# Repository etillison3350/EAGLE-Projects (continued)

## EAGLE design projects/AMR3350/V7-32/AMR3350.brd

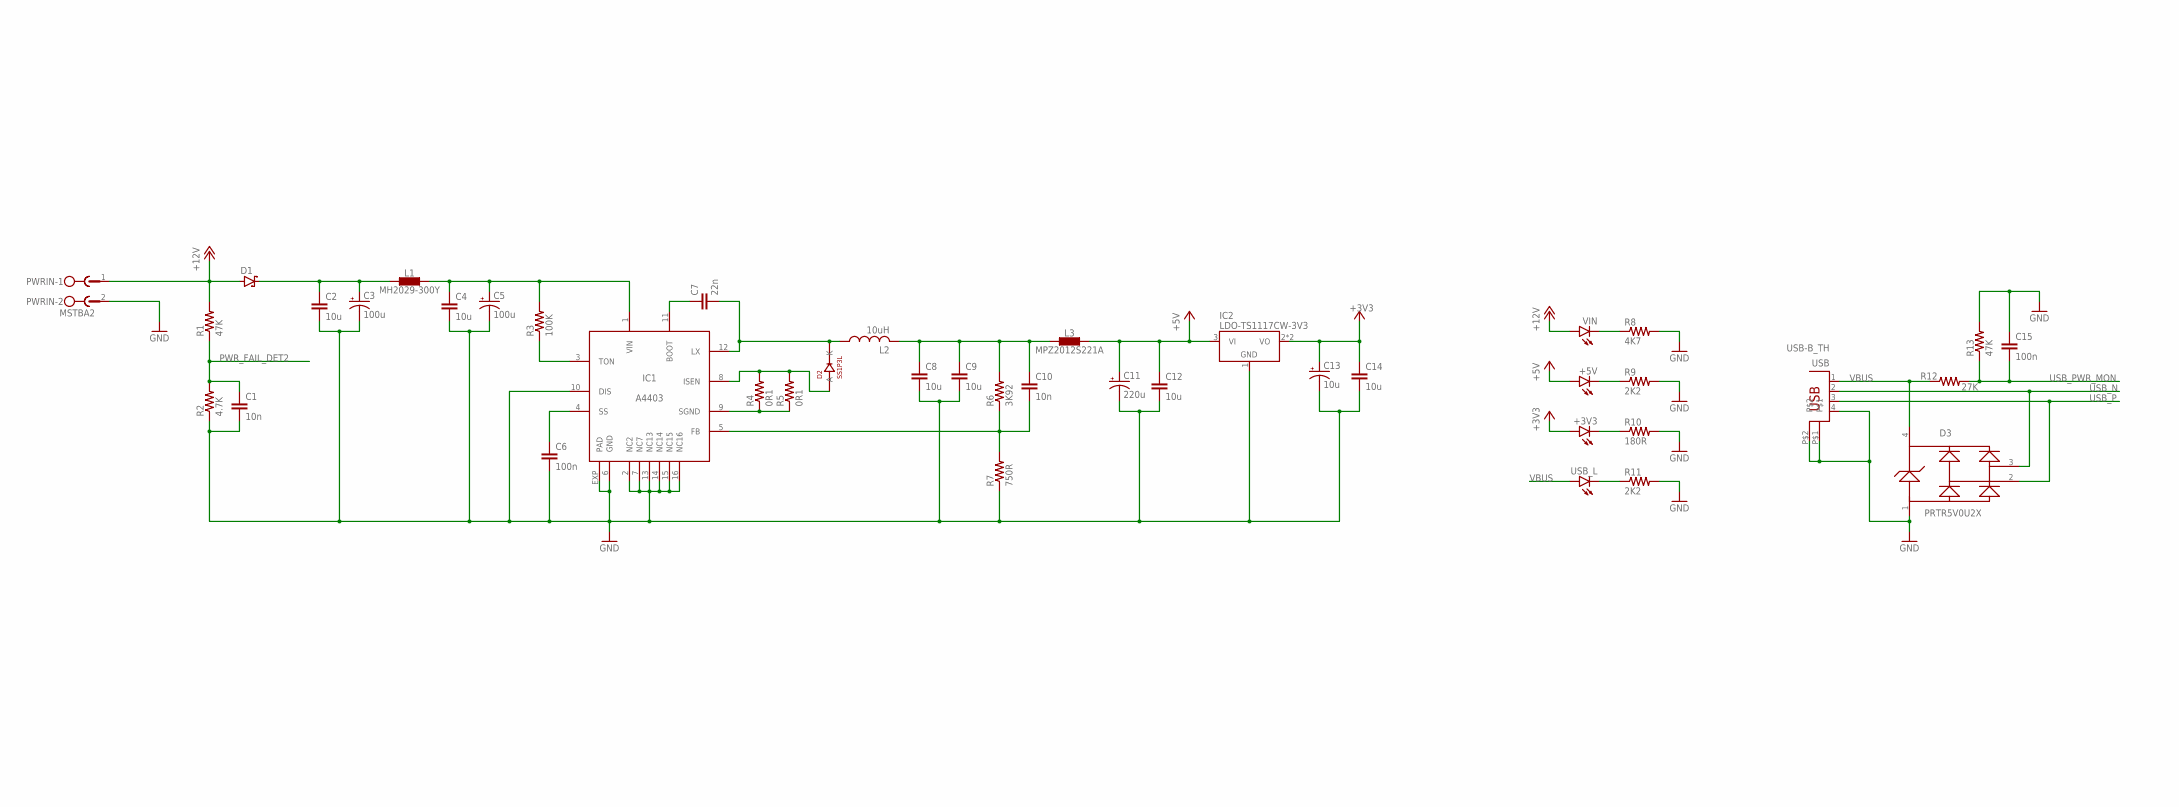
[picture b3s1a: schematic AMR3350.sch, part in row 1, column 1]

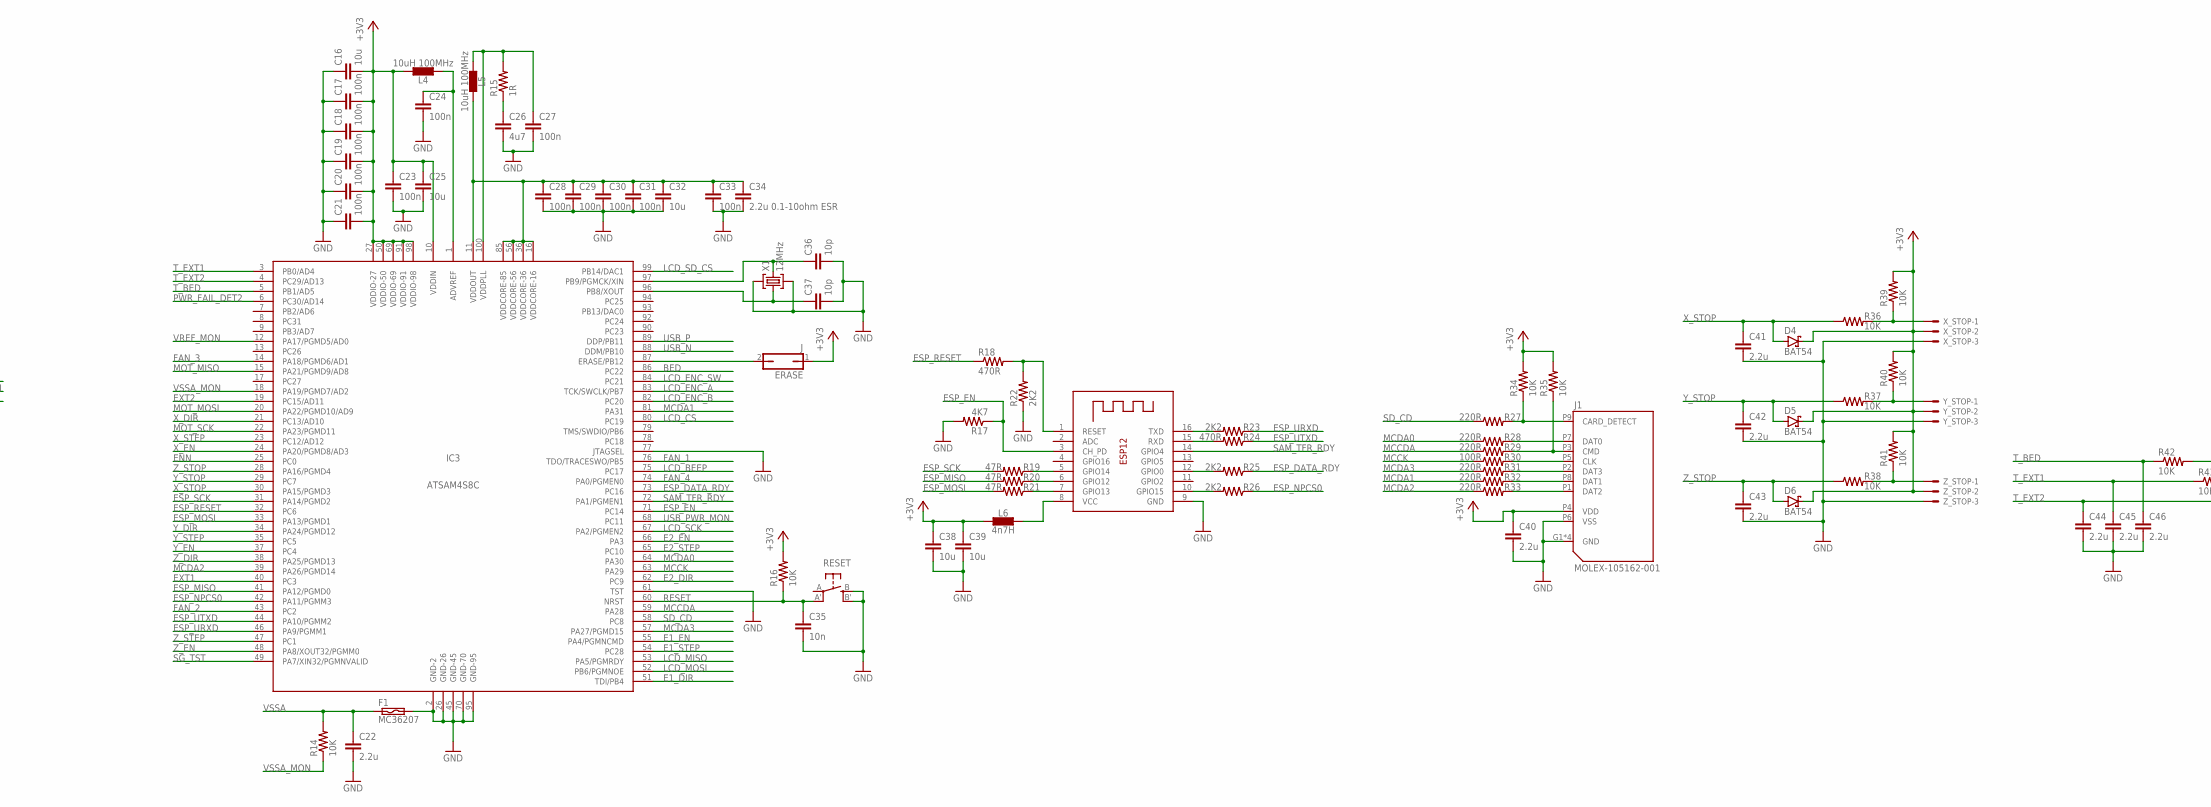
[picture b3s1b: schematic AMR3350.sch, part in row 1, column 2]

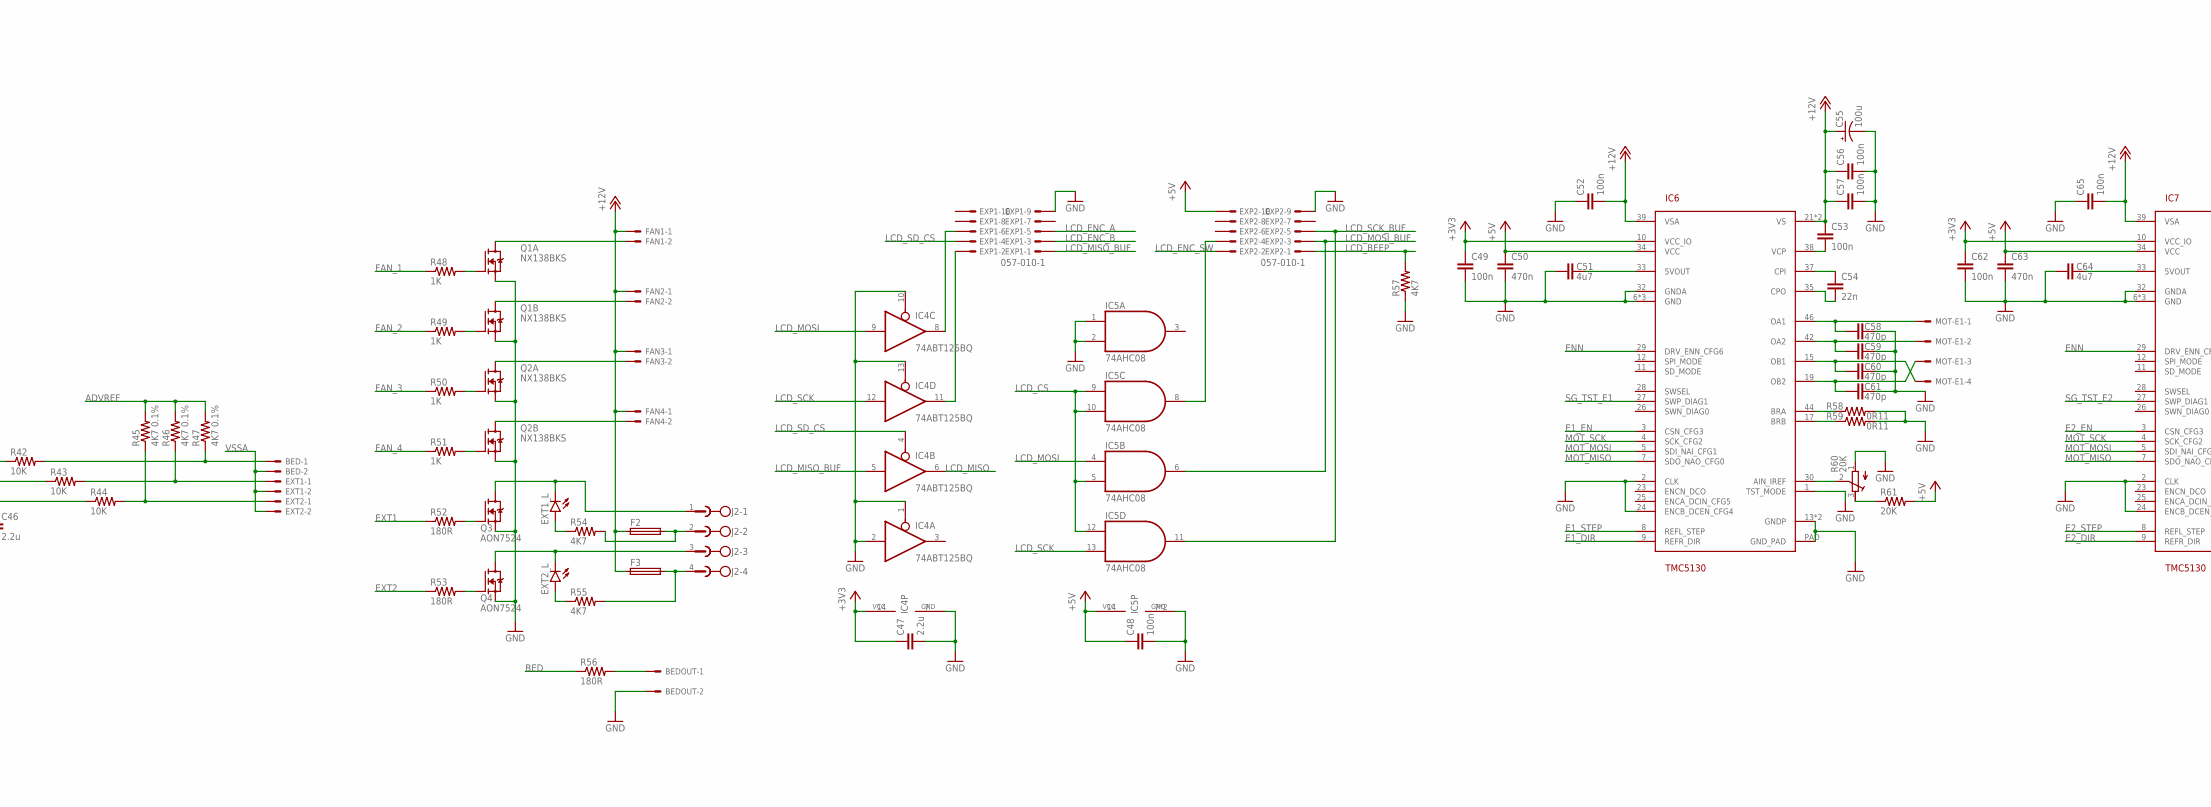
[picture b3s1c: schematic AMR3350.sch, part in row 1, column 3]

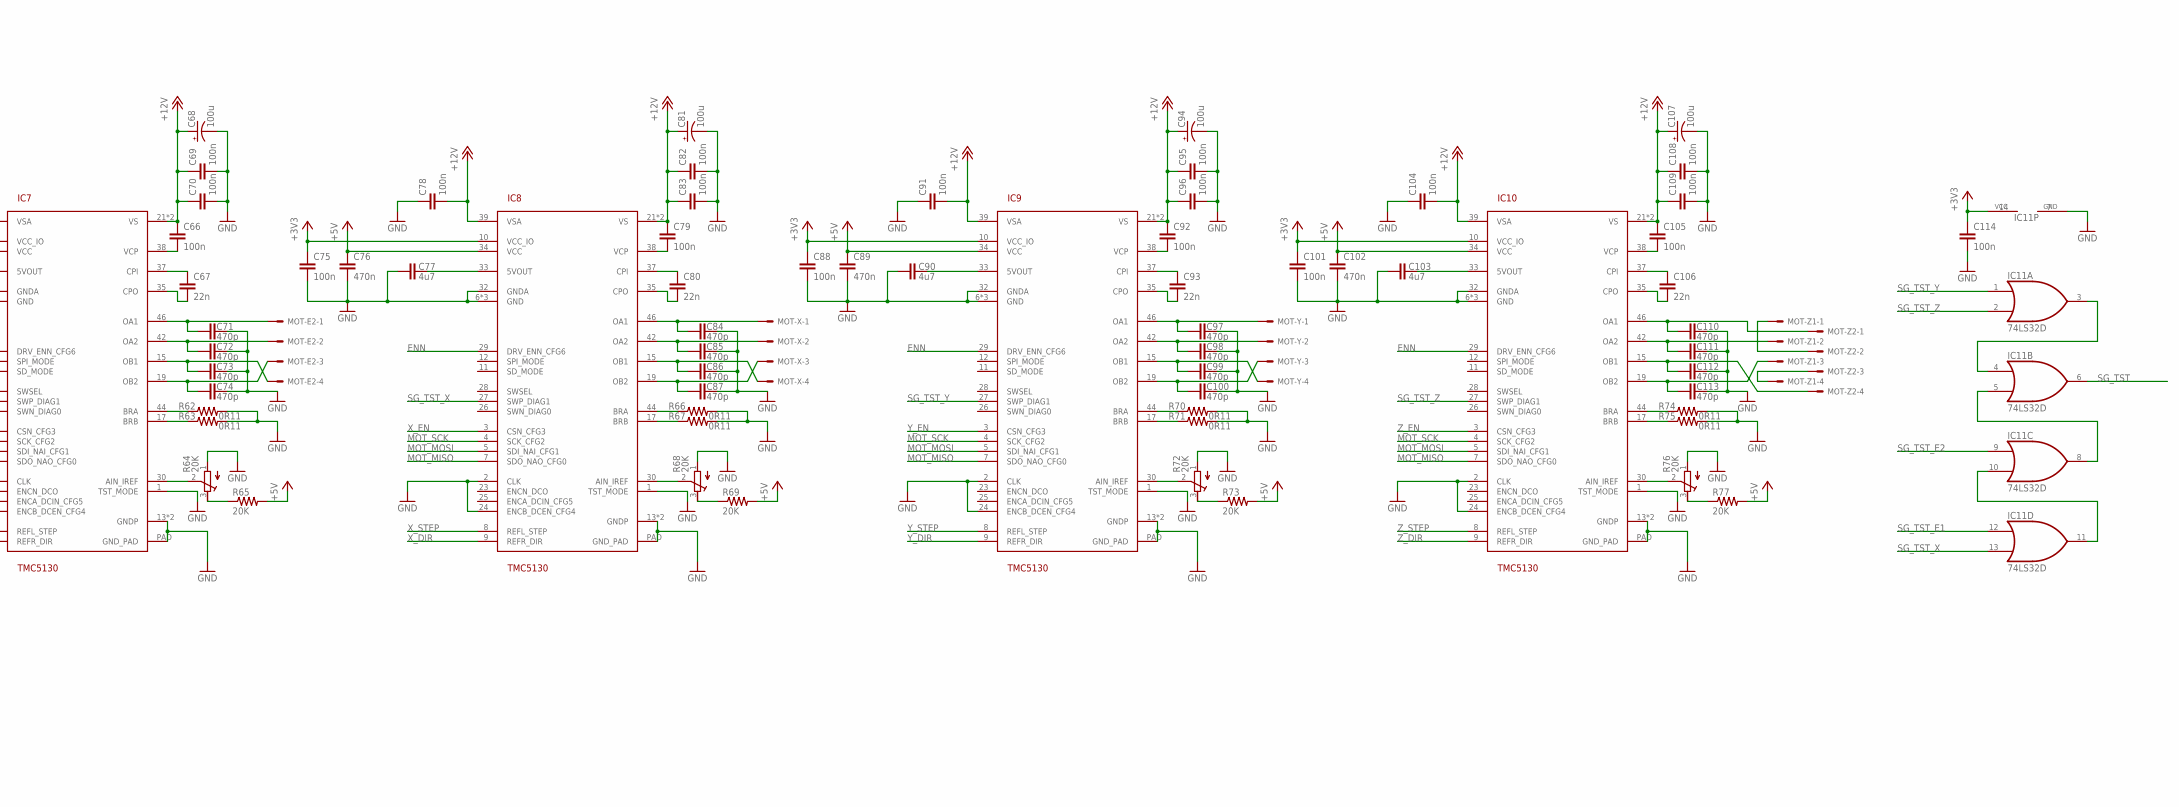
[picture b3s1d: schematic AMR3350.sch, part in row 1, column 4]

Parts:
+3V3, +5V: LEDCHIPLED_0805; CHIPLED_0805
BED: KK-254-2; MOLEX-KK-254-2
BEDOUT: KK-254-2; MOLEX-KK-254-2
C1, C10, C35: 10n; C0603
C2, C4, C8, C9, C12, C14, C25, C38, C39: 10u; C0603
C3, C5, C55, C68, C81, C94, C107: 100u; PANASONIC_D
C6, C15, C17, C18, C19, C20, C21, C23, C24, C27, C28, C29, C30, C31, C33, C48, C49, C52, C53, C56, C57, C62, C65, C66, C69, C70, C75, C78, C79, C82, C83, C88, C91, C92, C95, C96, C101, C104, C105, C108, C109, C114: 100n; C0603
C7, C54, C67, C80, C93, C106: 22n; C0603
C11: 220u; PANASONIC_D
C13: 10u; PANASONIC_D
C16, C32: 10u; C0805
C22, C40, C41, C42, C43, C44, C45, C46, C47: 2.2u; C0603
C26, C51, C64, C77, C90, C103: 4u7; C0603
C34: 2.2u 0.1-10ohm ESR; C0603
C36, C37: 10p; C0603
C50, C63, C76, C89, C102: 470n; C0603
C58, C59, C60, C61, C71, C72, C73, C74, C84, C85, C86, C87, C97, C98, C99, C100, C110, C111, C112, C113: 470p; C0402
D1: SCHOTTKY-DIODESMD; SMB
D2: SS1P3L; DO220AAL
D3: PRTR5V0U2XB; SOT143B
D4, D5, D6: BAT54; SOT23
ERASE: J; 1X02
ESP8266: ESP-12
EXP1, EXP2: 057-010-1
EXT1, EXT2: KK-254-2; MOLEX-KK-254-2
EXT1_L, EXT2_L: LEDCHIPLED_0805; CHIPLED_0805
F1: MC36207
F2, F3: 19560
FAN1, FAN2, FAN3, FAN4: KK-254-2; MOLEX-KK-254-2
IC1: A4403; QFN16-4X4
IC2: LDO-TS1117CW-3V3; SOT223
IC3: ATSAM4S8C; LQFP100
IC4: 74ABT125BQ; DHVQFN14
IC5: 74AHC08; DHVQFN14
IC6, IC7, IC8, IC9, IC10: TMC5130; QFP50P900X900X113-49N_NOFID
IC11: 74LS32D; SO14
J1: MOLEX-105162-001; MOLEX-105162
J2: MSTBV4
L1: MH2029-300Y; C0805
L2: 10uH; SRR0604
L3: MPZ2012S221A; C0805
L4, L5: 10uH 100MHz; C0603
L6: 4n7H; C0603
MOT-E1, MOT-E2: KK-254-4; MOLEX-KK-254-4
MOT-X: KK-254-4; MOLEX-KK-254-4
MOT-Y: KK-254-4; MOLEX-KK-254-4
MOT-Z1, MOT-Z2: KK-254-4; MOLEX-KK-254-4
PWRIN: MSTBA2
Q1, Q2: NX138BKS; SOT363_PHILIPS
Q3, Q4: AON7524; 3X3DFN-EP
R1, R13: 47K; R0603
R2: 4.7K; R0603
R3: 100K; R0603
R4, R5: 0R1; R0603
R6: 3K92; R0603
R7: 750R; R0603
R8, R17, R54, R55, R57: 4K7; R0603
R9, R11, R22, R23, R25, R26: 2K2; R0603
R10, R52, R53, R56: 180R; R0603
R12: 27K; R0603
R14, R16, R34, R35, R36, R37, R38, R39, R40, R41, R42, R43, R44: 10K; R0603
R15: 1R; R0603
R18, R24: 470R; R0603
R19, R20, R21: 47R; R0603
R27, R28, R29, R31, R32, R33: 220R; R0603
R30: 100R; R0603
R45, R46, R47: 4K7 0.1%; R0603
R48, R49, R50, R51: 1K; R0603
R58, R59, R62, R63, R66, R67, R70, R71, R74, R75: 0R11; R1206
R60, R64, R68, R72, R76: 20K; RTRIM3103
R61, R65, R69, R73, R77: 20K; R0603
RESET: EVQQ2
USB: USB-B_TH; PN61729
USB_L: LEDCHIPLED_0805; CHIPLED_0805
VIN: LEDCHIPLED_0805; CHIPLED_0805
X1: 12MHz; 5.0X3.2_KX-9A
X_STOP: KK-254-3; MOLEX-KK-254-3
Y_STOP: KK-254-3; MOLEX-KK-254-3
Z_STOP: KK-254-3; MOLEX-KK-254-3

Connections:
3V3_LED: +3V3.C, R10.1
5V_E1: C51.1, IC6.33 (5VOUT)
5V_E2: C64.1, IC7.33 (5VOUT)
5V_LED: +5V.C, R9.1
5V_X: C77.1, IC8.33 (5VOUT)
5V_Y: C90.1, IC9.33 (5VOUT)
5V_Z: C103.1, IC10.33 (5VOUT)
12V_LED: R8.1, VIN.C
+3V3: +3V3.A, C13.+, C14.1, C16.2, C17.2, C18.2, C19.2, C20.2, C21.2, C23.1, C25.1, C38.1, C39.1, C40.1, C47.1, C49.1, C62.1, C75.1, C88.1, C101.1, C114.1, D4.3 (C), D5.3 (C), D6.3 (C), ERASE.1, IC2.2 (VO), IC2.4 (VO), IC3.10 (VDDIN), IC3.27 (VDDIO-27), IC3.50 (VDDIO-50), IC3.69 (VDDIO-69), IC3.91 (VDDIO-91), IC3.98 (VDDIO-98), IC4.14 (VCC), IC6.10 (VCC_IO), IC7.10 (VCC_IO), IC8.10 (VCC_IO), IC9.10 (VCC_IO), IC10.10 (VCC_IO), IC11.14 (VCC), J1.P4 (VDD), L4.2, L6.1, R16.2, R34.2, R35.2, R39.2, R40.2, R41.2, X_STOP.2, Y_STOP.2, Z_STOP.2
+5V: +5V.A, C11.+, C12.1, C48.1, C50.1, C63.1, C76.1, C89.1, C102.1, EXP2.10, IC2.3 (VI), IC5.14 (VCC), IC6.34 (VCC), IC7.34 (VCC), IC8.34 (VCC), IC9.34 (VCC), IC10.34 (VCC), L3.2, R61.2, R65.2, R69.2, R73.2, R77.2
+12V: C52.2, C53.1, C55.+, C56.1, C57.1, C65.2, C66.1, C68.+, C69.1, C70.1, C78.2, C79.1, C81.+, C82.1, C83.1, C91.2, C92.1, C94.+, C95.1, C96.1, C104.2, C105.1, C107.+, C108.1, C109.1, D1.A, F2.1, F3.1, FAN1.1, FAN2.1, FAN3.1, FAN4.1, IC6.21 (VS), IC6.39 (VSA), IC6.40 (VS), IC7.21 (VS), IC7.39 (VSA), IC7.40 (VS), IC8.21 (VS), IC8.39 (VSA), IC8.40 (VS), IC9.21 (VS), IC9.39 (VSA), IC9.40 (VS), IC10.21 (VS), IC10.39 (VSA), IC10.40 (VS), PWRIN.1, R1.2, VIN.A
A1_E1: C58.1, IC6.46 (OA1), MOT-E1.1
A1_E2: C71.1, IC7.46 (OA1), MOT-E2.1
A1_X: C84.1, IC8.46 (OA1), MOT-X.1
A1_Y: C97.1, IC9.46 (OA1), MOT-Y.1
A1_Z: C110.1, IC10.46 (OA1), MOT-Z2.1
A2_E1: C59.1, IC6.42 (OA2), MOT-E1.2
A2_E2: C72.1, IC7.42 (OA2), MOT-E2.2
A2_X: C85.1, IC8.42 (OA2), MOT-X.2
A2_Y: C98.1, IC9.42 (OA2), MOT-Y.2
A2_Z: C111.1, IC10.42 (OA2), MOT-Z1.2
ADVREF: C24.1, IC3.1 (ADVREF), L4.1, R45.2, R46.2, R47.2
A_Z: MOT-Z1.1, MOT-Z2.2
B1_E1: C60.1, IC6.15 (OB1), MOT-E1.4
B1_E2: C73.1, IC7.15 (OB1), MOT-E2.4
B1_X: C86.1, IC8.15 (OB1), MOT-X.4
B1_Y: C99.1, IC9.15 (OB1), MOT-Y.4
B1_Z: C112.1, IC10.15 (OB1), MOT-Z2.4
B2_E1: C61.1, IC6.19 (OB2), MOT-E1.3
B2_E2: C74.1, IC7.19 (OB2), MOT-E2.3
B2_X: C87.1, IC8.19 (OB2), MOT-X.3
B2_Y: C100.1, IC9.19 (OB2), MOT-Y.3
B2_Z: C113.1, IC10.19 (OB2), MOT-Z1.3
BED: IC3.86 (PC22), R56.1
BED_L: EXT2_L.A, R55.1
BED_OUT: BEDOUT.1, R56.2
BOOT: C7.1, IC1.11 (BOOT)
BRA_E1: IC6.44 (BRA), R58.1
BRA_E2: IC7.44 (BRA), R62.1
BRA_X: IC8.44 (BRA), R66.1
BRA_Y: IC9.44 (BRA), R70.1
BRA_Z: IC10.44 (BRA), R74.1
BRB_E1: IC6.17 (BRB), R59.1
BRB_E2: IC7.17 (BRB), R63.1
BRB_X: IC8.17 (BRB), R67.1
BRB_Y: IC9.17 (BRB), R71.1
BRB_Z: IC10.17 (BRB), R75.1
B_Z: MOT-Z1.4, MOT-Z2.3
CLK: J1.P5 (CLK), R30.2
CMD: J1.P3 (CMD), R29.2, R35.1
CPI_E1: C54.1, IC6.37 (CPI)
CPI_E2: C67.1, IC7.37 (CPI)
CPI_X: C80.1, IC8.37 (CPI)
CPI_Y: C93.1, IC9.37 (CPI)
CPI_Z: C106.1, IC10.37 (CPI)
CPO_E1: C54.2, IC6.35 (CPO)
CPO_E2: C67.2, IC7.35 (CPO)
CPO_X: C80.2, IC8.35 (CPO)
CPO_Y: C93.2, IC9.35 (CPO)
CPO_Z: C106.2, IC10.35 (CPO)
DAT0: J1.P7 (DAT0), R28.2
DAT1: J1.P8 (DAT1), R32.2
DAT2: J1.P1 (DAT2), R33.2
DAT3: J1.P2 (DAT3), R31.2
DET: J1.P9 (CARD_DETECT), R27.2, R34.1
E1_DIR: IC3.51 (TDI/PB4), IC6.9 (REFR_DIR)
E1_EN: IC3.55 (PA4/PGMNCMD), IC6.3 (CSN_CFG3)
E1_FUSED: F2.2, J2.2, R54.2
E1_STEP: IC3.54 (PC28), IC6.8 (REFL_STEP)
E2_DIR: IC3.62 (PC9), IC7.9 (REFR_DIR)
E2_EN: IC3.66 (PA3), IC7.3 (CSN_CFG3)
E2_FUSED: F3.2, J2.4, R55.2
E2_STEP: IC3.65 (PC10), IC7.8 (REFL_STEP)
EDR_CONN: ESP8266.12 (GPIO0), R25.2
ENN: IC3.25 (PC0), IC6.29 (DRV_ENN_CFG6), IC7.29 (DRV_ENN_CFG6), IC8.29 (DRV_ENN_CFG6), IC9.29 (DRV_ENN_CFG6), IC10.29 (DRV_ENN_CFG6)
ERASE: ERASE.2, IC3.87 (ERASE/PB12)
ESP_CS: ESP8266.10 (GPIO15), R26.2
ESP_DATA_RDY: IC3.73 (PC16), R25.1
ESP_EN: ESP8266.3 (CH_PD), IC3.71 (PC14), R17.1
ESP_MISO: IC3.41 (PA12/PGMD0), R20.2
ESP_MOSI: IC3.33 (PA13/PGMD1), R21.2
ESP_NPCS0: IC3.42 (PA11/PGMM3), R26.1
ESP_RESET: IC3.32 (PC6), R18.1
ESP_RST: ESP8266.1 (RESET), R18.2, R22.2
ESP_RXD: ESP8266.16 (TXD), R23.2
ESP_SCK: IC3.31 (PA14/PGMD2), R19.2
ESP_TXD: ESP8266.15 (RXD), R24.2
ESP_URXD: IC3.46 (PA9/PGMM1), R23.1
ESP_UTXD: IC3.44 (PA10/PGMM2), R24.1
ESP_VIN: ESP8266.8 (VCC), L6.2
EXT1: IC3.40 (PC3), R52.1
EXT1_D: EXT1_L.C, J2.1, Q3.5 (D), Q3.6 (D), Q3.7 (D), Q3.8 (D), Q3.E1 (D), Q3.E2 (D), Q3.PAD (D)
EXT1_G: Q3.4 (G), R52.2
EXT2: IC3.19 (PC15/AD11), R53.1
EXT2_D: EXT2_L.C, J2.3, Q4.5 (D), Q4.6 (D), Q4.7 (D), Q4.8 (D), Q4.E1 (D), Q4.E2 (D), Q4.PAD (D)
EXT2_G: Q4.4 (G), R53.2
EXT_L: EXT1_L.A, R54.1
FAN1_D: FAN1.2, Q1.6 (D)
FAN1_G: Q1.2 (G), R48.2
FAN2_D: FAN2.2, Q1.3 (D)
FAN2_G: Q1.5 (G), R49.2
FAN3_D: FAN3.2, Q2.6 (D)
FAN3_G: Q2.2 (G), R50.2
FAN4_D: FAN4.2, Q2.3 (D)
FAN4_G: Q2.5 (G), R51.2
FAN_1: IC3.76 (TDO/TRACESWO/PB5), R48.1
FAN_2: IC3.43 (PC2), R49.1
FAN_3: IC3.14 (PA18/PGMD6/AD1), R50.1
FAN_4: IC3.74 (PA0/PGMEN0), R51.1
FB: C10.2, IC1.5 (FB), R6.1, R7.2
GND: BEDOUT.2, C1.2, C2.2, C3.-, C4.2, C5.-, C6.2, C8.2, C9.2, C11.-, C12.2, C13.-, C14.2, C15.1, C16.1, C17.1, C18.1, C19.1, C20.1, C21.1, C22.2, C23.2, C24.2, C25.2, C26.2, C27.2, C28.2, C29.2, C30.2, C31.2, C32.2, C33.2, C34.2, C35.2, C36.2, C37.2, C38.2, C39.2, C40.2, C41.2, C42.2, C43.2, C44.2, C45.2, C46.2, C47.2, C48.2, C49.2, C50.2, C51.2, C52.1, C55.-, C56.2, C57.2, C58.2, C59.2, C60.2, C61.2, C62.2, C63.2, C64.2, C65.1, C68.-, C69.2, C70.2, C71.2, C72.2, C73.2, C74.2, C75.2, C76.2, C77.2, C78.1, C81.-, C82.2, C83.2, C84.2, C85.2, C86.2, C87.2, C88.2, C89.2, C90.2, C91.1, C94.-, C95.2, C96.2, C97.2, C98.2, C99.2, C100.2, C101.2, C102.2, C103.2, C104.1, C107.-, C108.2, C109.2, C110.2, C111.2, C112.2, C113.2, C114.2, D3.1, ESP8266.9 (GND), EXP1.9, EXP2.9, F1.2, IC1.2 (NC2), IC1.6 (GND), IC1.7 (NC7), IC1.10 (DIS), IC1.13 (NC13), IC1.14 (NC14), IC1.15 (NC15), IC1.16 (NC16), IC1.EXP (PAD), IC2.1 (GND), IC3.2 (GND-2), IC3.26 (GND-26), IC3.45 (GND-45), IC3.61 (TST), IC3.70 (GND-70), IC3.77 (JTAGSEL), IC3.95 (GND-95), IC4.1 (OE), IC4.2 (I), IC4.7 (GND), IC4.10 (OE), IC4.13 (OE), IC5.1 (I0), IC5.2 (I1), IC5.7 (GND), IC5.EXP (GND), IC6.1 (TST_MODE), IC6.2 (CLK), IC6.6 (GND), IC6.13 (GNDP), IC6.24 (ENCB_DCEN_CFG4), IC6.31 (GND), IC6.32 (GNDA), IC6.36 (GND), IC6.48 (GNDP), IC6.PAD (GND_PAD), IC7.1 (TST_MODE), IC7.2 (CLK), IC7.6 (GND), IC7.13 (GNDP), IC7.24 (ENCB_DCEN_CFG4), IC7.31 (GND), IC7.32 (GNDA), IC7.36 (GND), IC7.48 (GNDP), IC7.PAD (GND_PAD), IC8.1 (TST_MODE), IC8.2 (CLK), IC8.6 (GND), IC8.13 (GNDP), IC8.24 (ENCB_DCEN_CFG4), IC8.31 (GND), IC8.32 (GNDA), IC8.36 (GND), IC8.48 (GNDP), IC8.PAD (GND_PAD), IC9.1 (TST_MODE), IC9.2 (CLK), IC9.6 (GND), IC9.13 (GNDP), IC9.24 (ENCB_DCEN_CFG4), IC9.31 (GND), IC9.32 (GNDA), IC9.36 (GND), IC9.48 (GNDP), IC9.PAD (GND_PAD), IC10.1 (TST_MODE), IC10.2 (CLK), IC10.6 (GND), IC10.13 (GNDP), IC10.24 (ENCB_DCEN_CFG4), IC10.31 (GND), IC10.32 (GNDA), IC10.36 (GND), IC10.48 (GNDP), IC10.PAD (GND_PAD), IC11.7 (GND), J1.G1 (GND), J1.G2 (GND), J1.G3 (GND), J1.G4 (GND), J1.P6 (VSS), PWRIN.2, Q1.1 (S), Q1.4 (S), Q2.1 (S), Q2.4 (S), Q3.1 (S), Q3.2 (S), Q3.3 (S), Q4.1 (S), Q4.2 (S), Q4.3 (S), R2.1, R7.1, R8.2, R9.2, R10.2, R11.2, R13.2, R17.2, R22.1, R57.1, R58.2, R59.2, R60.1 (A), R62.2, R63.2, R64.1 (A), R66.2, R67.2, R68.1 (A), R70.2, R71.2, R72.1 (A), R74.2, R75.2, R76.1 (A), RESET.B (S), RESET.B' (S1), USB.4, USB.P$1, USB.P$2, X1.2, X1.4, X_STOP.3, Y_STOP.3, Z_STOP.3
IDEK: C26.1, R15.1
IREF_E1: IC6.30 (AIN_IREF), R60.2 (S)
IREF_E2: IC7.30 (AIN_IREF), R64.2 (S)
IREF_X: IC8.30 (AIN_IREF), R68.2 (S)
IREF_Y: IC9.30 (AIN_IREF), R72.2 (S)
IREF_Z: IC10.30 (AIN_IREF), R76.2 (S)
ISEN: D2.P$2 (A), IC1.8 (ISEN), R4.2, R5.2
LCD_BEEP: EXP2.1, IC3.75 (PC17), R57.2
LCD_CS: IC3.80 (PC19), IC5.5 (I1), IC5.9 (I0), IC5.10 (I1), IC5.12 (I0)
LCD_CS_BUF: EXP2.4, IC5.8 (O)
LCD_ENC_A: EXP1.5, IC3.83 (TCK/SWCLK/PB7)
LCD_ENC_B: EXP1.3, IC3.82 (PC20)
LCD_ENC_SW: EXP2.2, IC3.84 (PC21)
LCD_MISO: IC3.53 (PA5/PGMRDY), IC4.6 (O)
LCD_MISO_BUF: EXP1.1, IC4.5 (I)
LCD_MOSI: IC3.52 (PB6/PGMNOE), IC4.9 (I), IC5.4 (I0)
LCD_MOSI_BUF: EXP2.3, IC5.6 (O)
LCD_SCK: IC3.67 (PA2/PGMEN2), IC4.12 (I), IC5.13 (I1)
LCD_SCK_BUF: EXP2.5, IC5.11 (O)
LCD_SD_CS: EXP1.4, IC3.99 (PB14/DAC1), IC4.4 (OE)
LX: C7.2, D2.P$1 (K), IC1.12 (LX), L2.P$1 (1)
MCCDA: IC3.59 (PA28), R29.1
MCCK: IC3.63 (PA29), R30.1
MCDA0: IC3.64 (PA30), R28.1
MCDA1: IC3.81 (PA31), R32.1
MCDA2: IC3.39 (PA26/PGMD14), R33.1
MCDA3: IC3.57 (PA27/PGMD15), R31.1
MISO: ESP8266.6 (GPIO12), R20.1
MOSI: ESP8266.7 (GPIO13), R21.1
MOT_MISO: IC3.15 (PA21/PGMD9/AD8), IC6.7 (SDO_NAO_CFG0), IC7.7 (SDO_NAO_CFG0), IC8.7 (SDO_NAO_CFG0), IC9.7 (SDO_NAO_CFG0), IC10.7 (SDO_NAO_CFG0)
MOT_MOSI: IC3.20 (PA22/PGMD10/AD9), IC6.5 (SDI_NAI_CFG1), IC7.5 (SDI_NAI_CFG1), IC8.5 (SDI_NAI_CFG1), IC9.5 (SDI_NAI_CFG1), IC10.5 (SDI_NAI_CFG1)
MOT_SCK: IC3.22 (PA23/PGMD11), IC6.4 (SCK_CFG2), IC7.4 (SCK_CFG2), IC8.4 (SCK_CFG2), IC9.4 (SCK_CFG2), IC10.4 (SCK_CFG2)
PWR_FAIL_DET2: C1.1, IC3.6 (PC30/AD14), R1.1, R2.2
REFIN_E1: R60.3 (E), R61.1
REFIN_E2: R64.3 (E), R65.1
REFIN_X: R68.3 (E), R69.1
REFIN_Y: R72.3 (E), R73.1
REFIN_Z: R76.3 (E), R77.1
RESET: C35.1, IC3.60 (NRST), R16.1, RESET.A' (P1)
SAM_TFR_RDY: ESP8266.14 (GPIO4), IC3.72 (PA1/PGMEN1)
SD_CD: IC3.58 (PC8), R27.1
SD_MOSI_BUF: EXP1.6, IC4.8 (O)
SD_SCK_BUF: EXP1.2, IC4.11 (O)
SGND: IC1.9 (SGND), R4.1, R5.1
SG_TST: IC3.49 (PA7/XIN32/PGMNVALID), IC11.6 (O)
SG_TST_E1: IC6.27 (SWP_DIAG1), IC11.12 (I0)
SG_TST_E1X: IC11.10 (I1), IC11.11 (O)
SG_TST_E2: IC7.27 (SWP_DIAG1), IC11.9 (I0)
SG_TST_EX: IC11.5 (I1), IC11.8 (O)
SG_TST_X: IC8.27 (SWP_DIAG1), IC11.13 (I1)
SG_TST_Y: IC9.27 (SWP_DIAG1), IC11.1 (I0)
SG_TST_YZ: IC11.3 (O), IC11.4 (I0)
SG_TST_Z: IC10.27 (SWP_DIAG1), IC11.2 (I1)
SPCK: ESP8266.5 (GPIO14), R19.1
SS: C6.1, IC1.4 (SS)
TON: IC1.3 (TON), R3.1
T_BED: C46.1, IC3.5 (PB1/AD5), R42.1
T_BED_IN: BED.1, R42.2, R47.1
T_EXT1: C45.1, IC3.3 (PB0/AD4), R43.1
T_EXT2: C44.1, IC3.4 (PC29/AD13), R44.1
T_EXT_IN1: EXT1.1, R43.2, R46.1
T_EXT_IN2: EXT2.1, R44.2, R45.1
USB_LED: R11.1, USB_L.C
USB_N: D3.3, IC3.88 (DDM/PB10), USB.2
USB_P: D3.2, IC3.89 (DDP/PB11), USB.3
USB_PWR_MON: C15.2, IC3.68 (PC11), R12.2, R13.1
VBUS: D3.4, R12.1, USB.1, USB_L.A
VCP_E1: C53.2, IC6.38 (VCP)
VCP_E2: C66.2, IC7.38 (VCP)
VCP_X: C79.2, IC8.38 (VCP)
VCP_Y: C92.2, IC9.38 (VCP)
VCP_Z: C105.2, IC10.38 (VCP)
VDDOUT: C28.1, C29.1, C30.1, C31.1, C32.1, C33.1, C34.1, IC3.11 (VDDOUT), IC3.16 (VDDCORE-16), IC3.36 (VDDCORE-36), IC3.56 (VDDCORE-56), IC3.85 (VDDCORE-85), L5.2
VDDPLL: C27.1, IC3.100 (VDDPLL), L5.1, R15.2
VIN: C2.1, C3.+, D1.C, L1.1
VIN_F: C4.1, C5.+, IC1.1 (VIN), L1.2, R3.2
VOUT: C8.1, C9.1, C10.1, L2.P$2 (2), L3.1, R6.2
VREF_MON: IC3.12 (PA17/PGMD5/AD0)
VSSA: BED.2, C22.1, EXT1.2, EXT2.2, F1.1, R14.2
VSSA_MON: IC3.18 (PA19/PGMD7/AD2), R14.1
XIN: C36.1, IC3.97 (PB9/PGMCK/XIN), X1.3
XOUT: C37.1, IC3.96 (PB8/XOUT), X1.1
X_DIR: IC3.21 (PC13/AD10), IC8.9 (REFR_DIR)
X_EN: IC3.24 (PA20/PGMD8/AD3), IC8.3 (CSN_CFG3)
X_STEP: IC3.23 (PC12/AD12), IC8.8 (REFL_STEP)
X_STOP: C41.1, D4.1 (A), IC3.30 (PA15/PGMD3), R36.1
X_STOP_IN: R36.2, R39.1, X_STOP.1
Y_DIR: IC3.34 (PA24/PGMD12), IC9.9 (REFR_DIR)
Y_EN: IC3.37 (PC4), IC9.3 (CSN_CFG3)
Y_STEP: IC3.35 (PC5), IC9.8 (REFL_STEP)
Y_STOP: C42.1, D5.1 (A), IC3.29 (PC7), R37.1
Y_STOP_IN: R37.2, R40.1, Y_STOP.1
Z_DIR: IC3.38 (PA25/PGMD13), IC10.9 (REFR_DIR)
Z_EN: IC3.48 (PA8/XOUT32/PGMM0), IC10.3 (CSN_CFG3)
Z_STEP: IC3.47 (PC1), IC10.8 (REFL_STEP)
Z_STOP: C43.1, D6.1 (A), IC3.28 (PA16/PGMD4), R38.1
Z_STOP_IN: R38.2, R41.1, Z_STOP.1

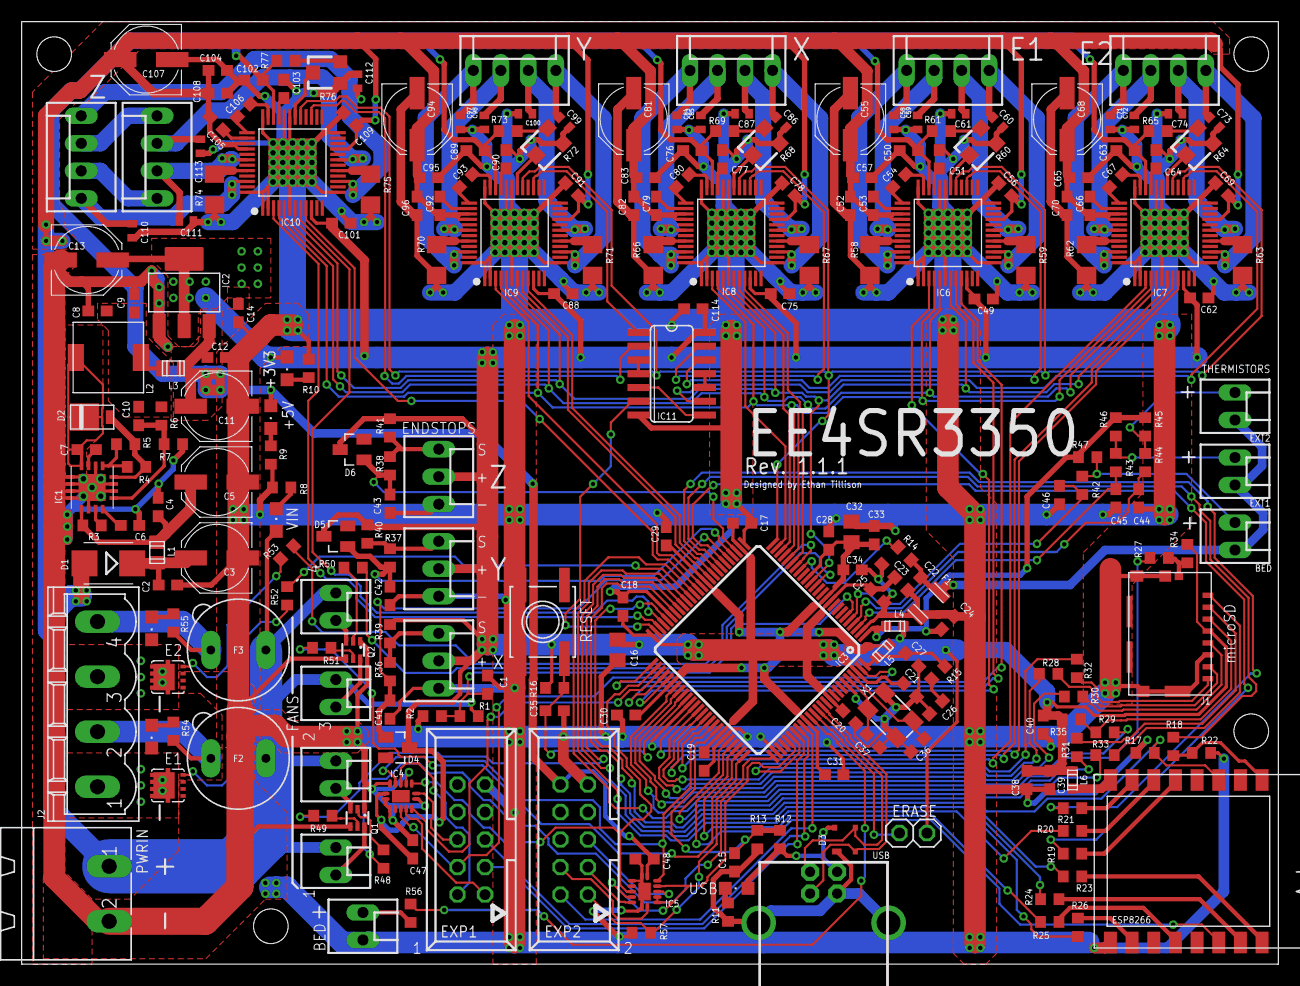
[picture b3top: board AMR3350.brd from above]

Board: 2 copper layers, 116.0 x 87.0 mm, 254 parts (0 on the bottom side), 207 nets.

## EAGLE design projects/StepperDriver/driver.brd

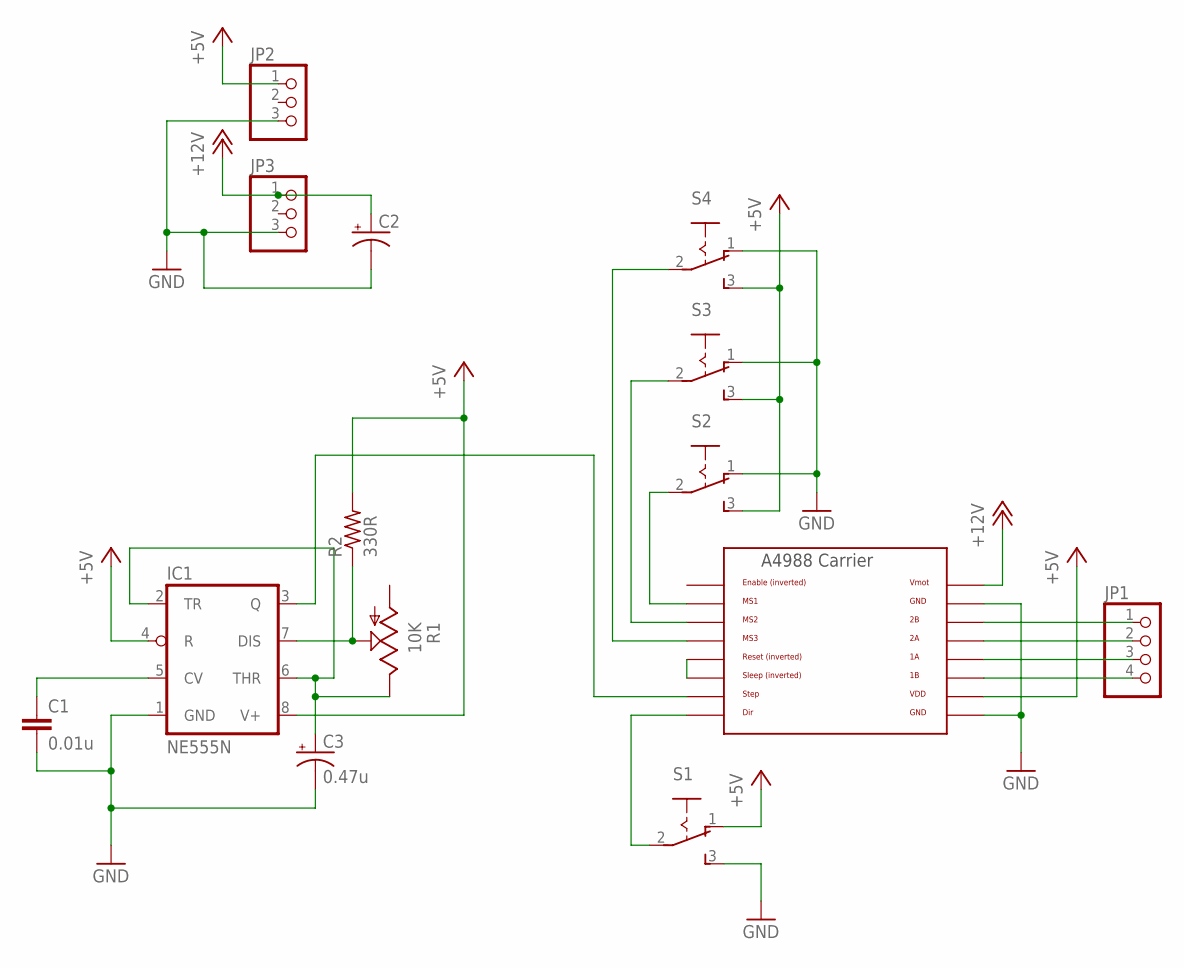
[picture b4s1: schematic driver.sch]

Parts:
C1: 0.01u; C0603
C2: CPOL-USE5-6; E5-6
C3: 0.47u; E2,5-6E
IC1: NE555N; DIL08
JP1: PINHD-1X4/90; 1X04/90
JP2, JP3: PINHD-1X3; 1X03
R1: 10K; RJ9W
R2: 330R; R0603
S1, S2, S3, S4: M251
U$1: A4988BREAKOUT

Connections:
+5V: IC1.4 (R), IC1.8 (V+), JP2.1, R2.2, S1.1 (O), S2.3 (S), S3.3 (S), S4.3 (S), U$1.VDD
+12V: C2.+, JP3.1, U$1.VMOT
GND: C1.2, C2.-, C3.-, IC1.1 (GND), JP2.3, JP3.3, S1.3 (S), S2.1 (O), S3.1 (O), S4.1 (O), U$1.GND, U$1.GND@0 (GND)
unnamed: S1.2, U$1.DIR
unnamed: U$1.RST, U$1.SLP (SLEEP)
unnamed: S2.2, U$1.MS1
unnamed: S3.2, U$1.MS2
unnamed: S4.2, U$1.MS3
unnamed: JP1.1, U$1.2B
unnamed: JP1.2, U$1.2A
unnamed: JP1.3, U$1.1A
unnamed: JP1.4, U$1.1B
unnamed: IC1.3 (Q), U$1.STEP
unnamed: IC1.7 (DIS), R1.S, R2.1
unnamed: C3.+, IC1.2 (TR), IC1.6 (THR), R1.E
unnamed: C1.1, IC1.5 (CV)

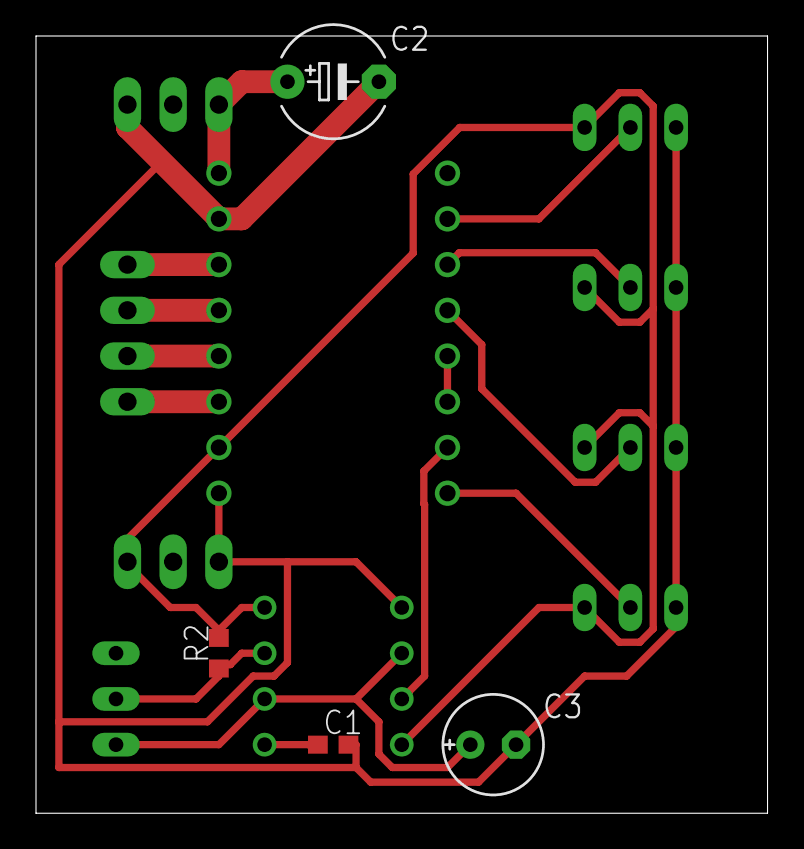
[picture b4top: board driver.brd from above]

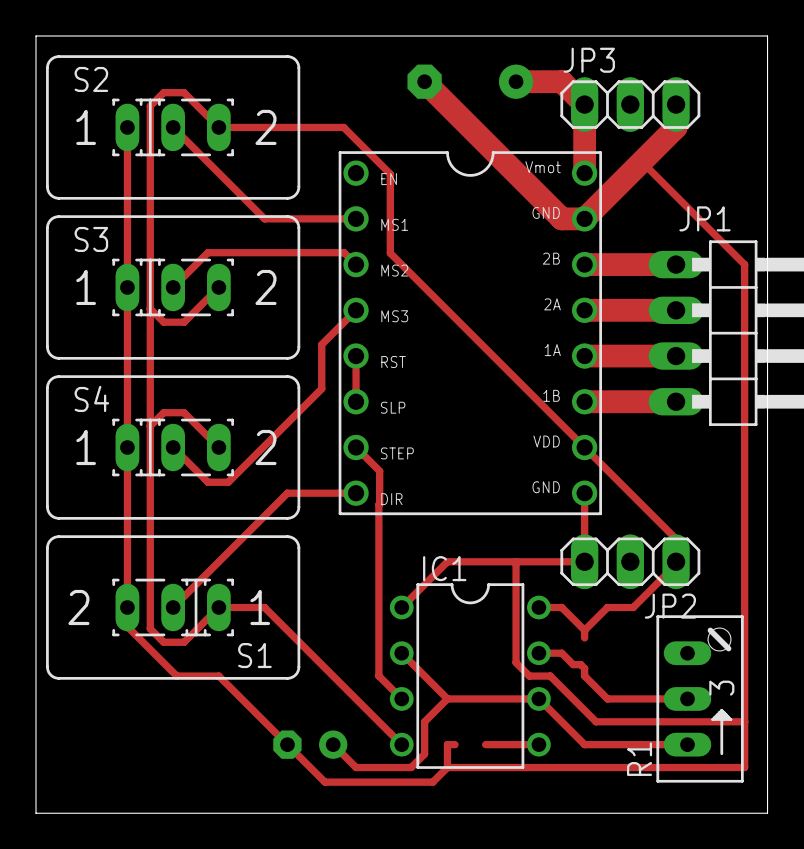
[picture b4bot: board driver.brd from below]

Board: 2 copper layers, 40.6 x 43.2 mm, 14 parts (10 on the bottom side), 16 nets.

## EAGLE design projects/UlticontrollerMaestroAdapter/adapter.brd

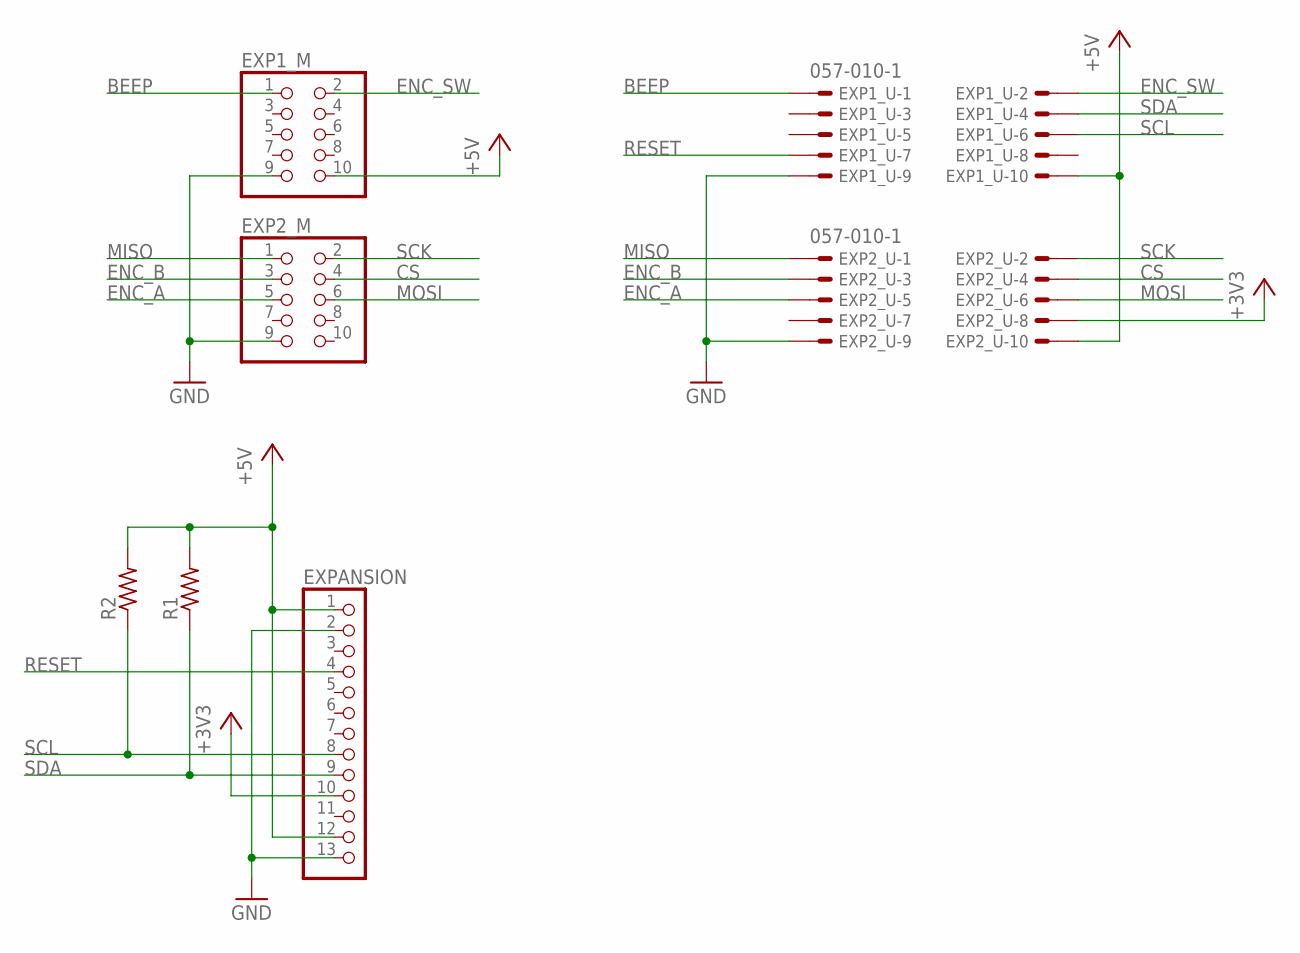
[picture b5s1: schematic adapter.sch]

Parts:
EXP1_M, EXP2_M: PINHD-2X5; 2X05
EXP1_U, EXP2_U: 057-010-1
EXPANSION: PINHD-1X13; 1X13
R1, R2: R-US_0204/7; 0204/7

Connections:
+3V3: EXP2_U.8, EXPANSION.10
+5V: EXP1_M.10, EXP1_U.10, EXP2_U.10, EXPANSION.1, EXPANSION.12, R1.2, R2.2
BEEP: EXP1_M.1, EXP1_U.1
CS: EXP2_M.4, EXP2_U.4
ENC_A: EXP2_M.5, EXP2_U.5
ENC_B: EXP2_M.3, EXP2_U.3
ENC_SW: EXP1_M.2, EXP1_U.2
GND: EXP1_M.9, EXP1_U.9, EXP2_M.9, EXP2_U.9, EXPANSION.2, EXPANSION.13
MISO: EXP2_M.1, EXP2_U.1
MOSI: EXP2_M.6, EXP2_U.6
RESET: EXP1_U.7, EXPANSION.4
SCK: EXP2_M.2, EXP2_U.2
SCL: EXP1_U.6, EXPANSION.8, R2.1
SDA: EXP1_U.4, EXPANSION.9, R1.1

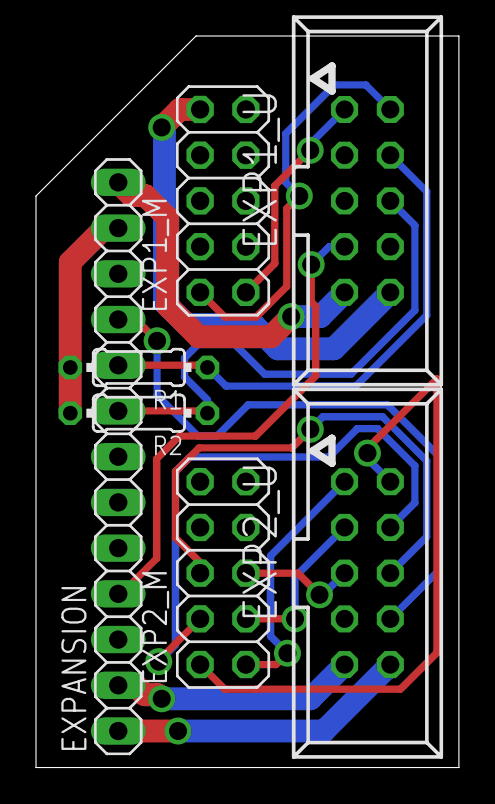
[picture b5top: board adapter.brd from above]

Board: 2 copper layers, 23.5 x 40.6 mm, 7 parts (0 on the bottom side), 14 nets.
